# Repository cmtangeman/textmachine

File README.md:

# TextMachine
CrankPhone SW/FW/HW/Mech
Notes on directory structure:

FW:

ArduinoILI9341MKNNB1500 :  All for resistive touch FW (old)

capTouchTestingAndCal: testing calibration of capacitive touch

receiveSMSwithDebug:  debug file that doesn't need touchscreen

techmach: FW for old resistive screen

techmachcap: FW for current working capacitive touch screen.  See README.txt in this directory for further info.

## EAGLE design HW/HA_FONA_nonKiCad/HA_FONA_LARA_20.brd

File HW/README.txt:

Herein lies the HW, including board design, BOM, physical design, etc.  

The plan is to delta from the known working feather FONA board and fit it into current CrankLite PCB form factor.
This would make the physical design changes minimal, though a few cleanups to the physical design may occur.

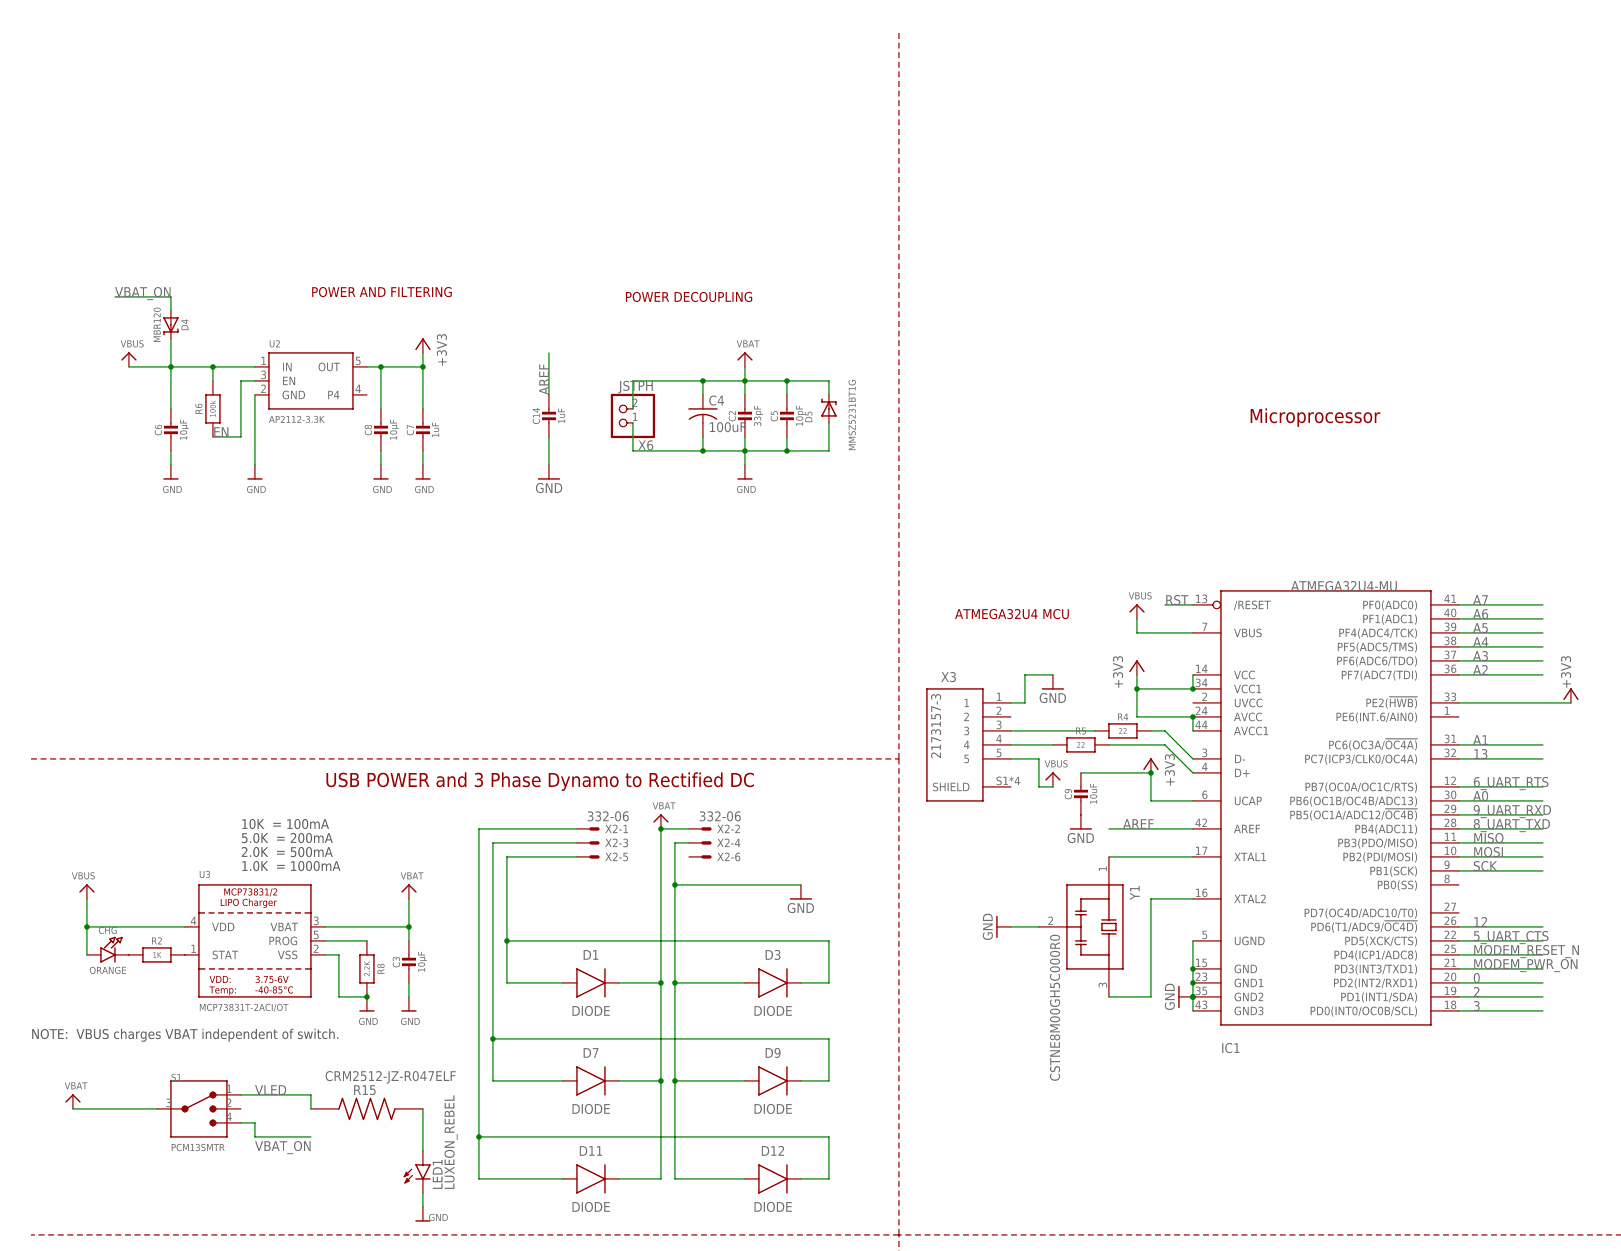
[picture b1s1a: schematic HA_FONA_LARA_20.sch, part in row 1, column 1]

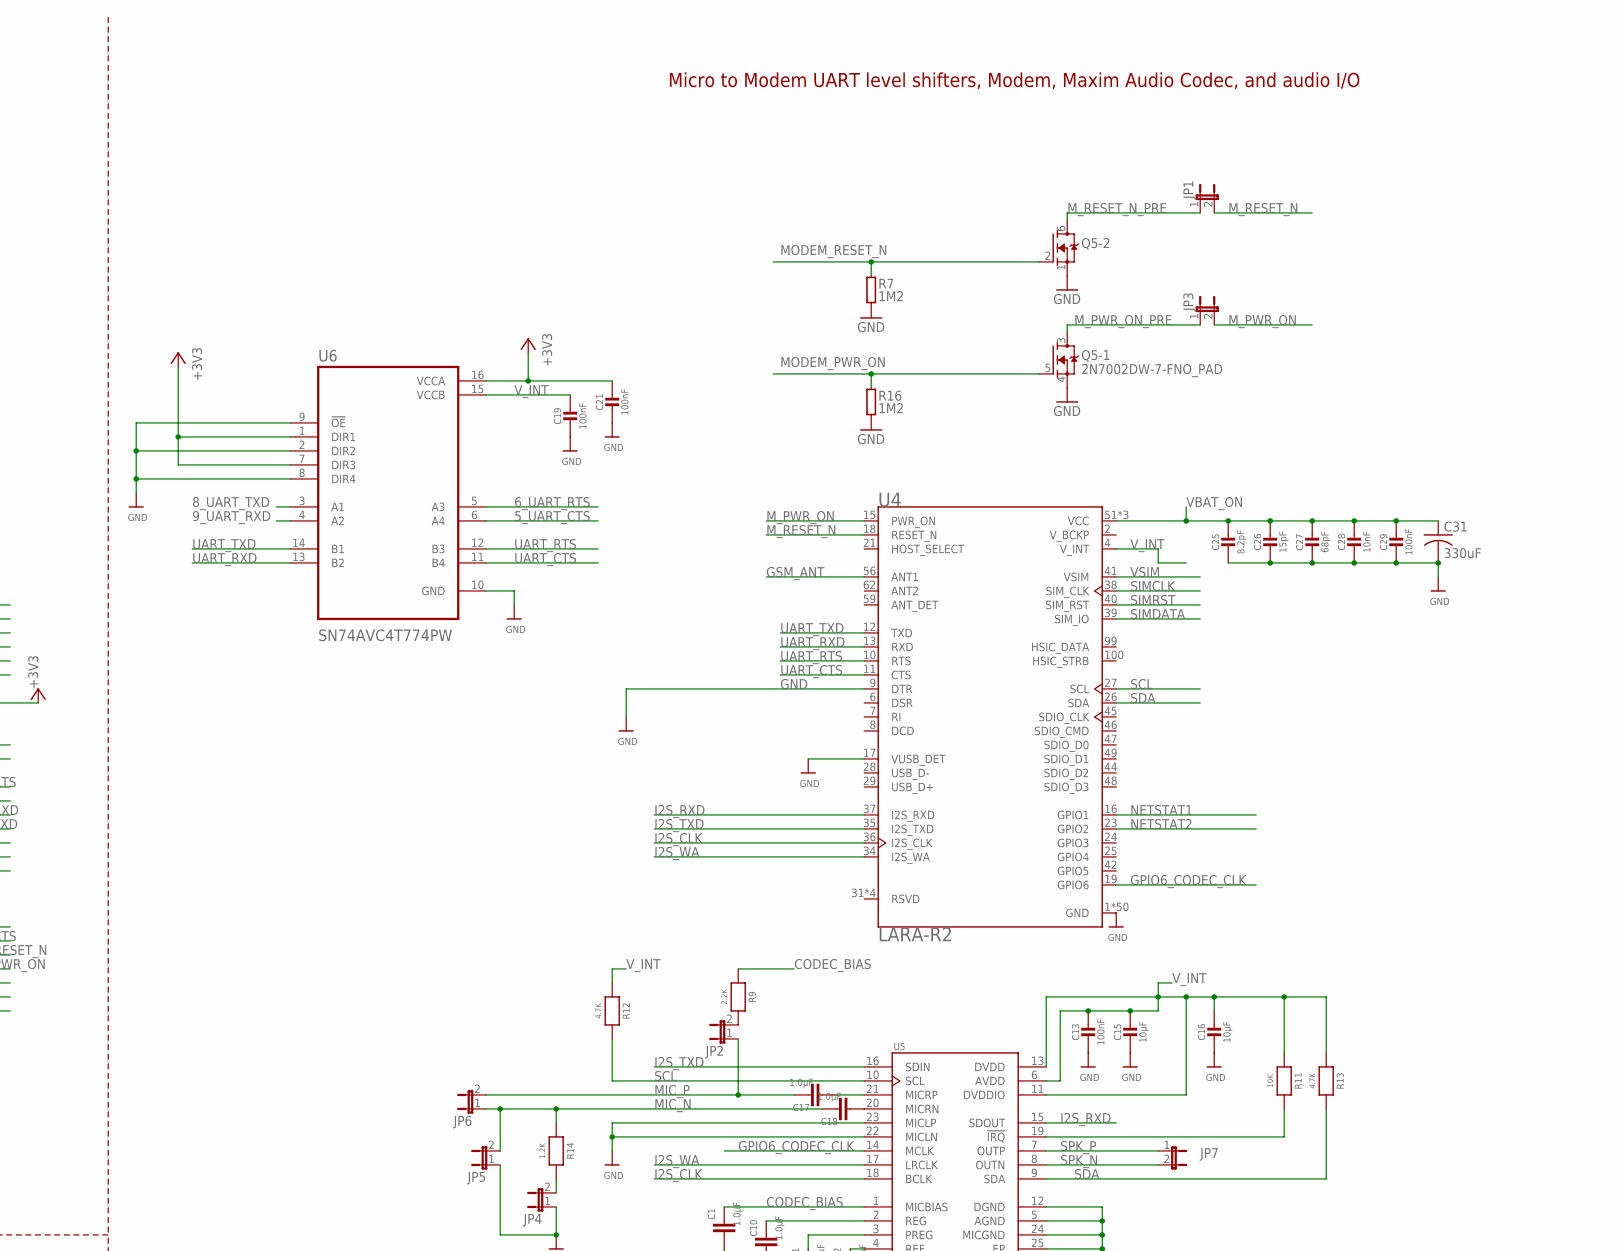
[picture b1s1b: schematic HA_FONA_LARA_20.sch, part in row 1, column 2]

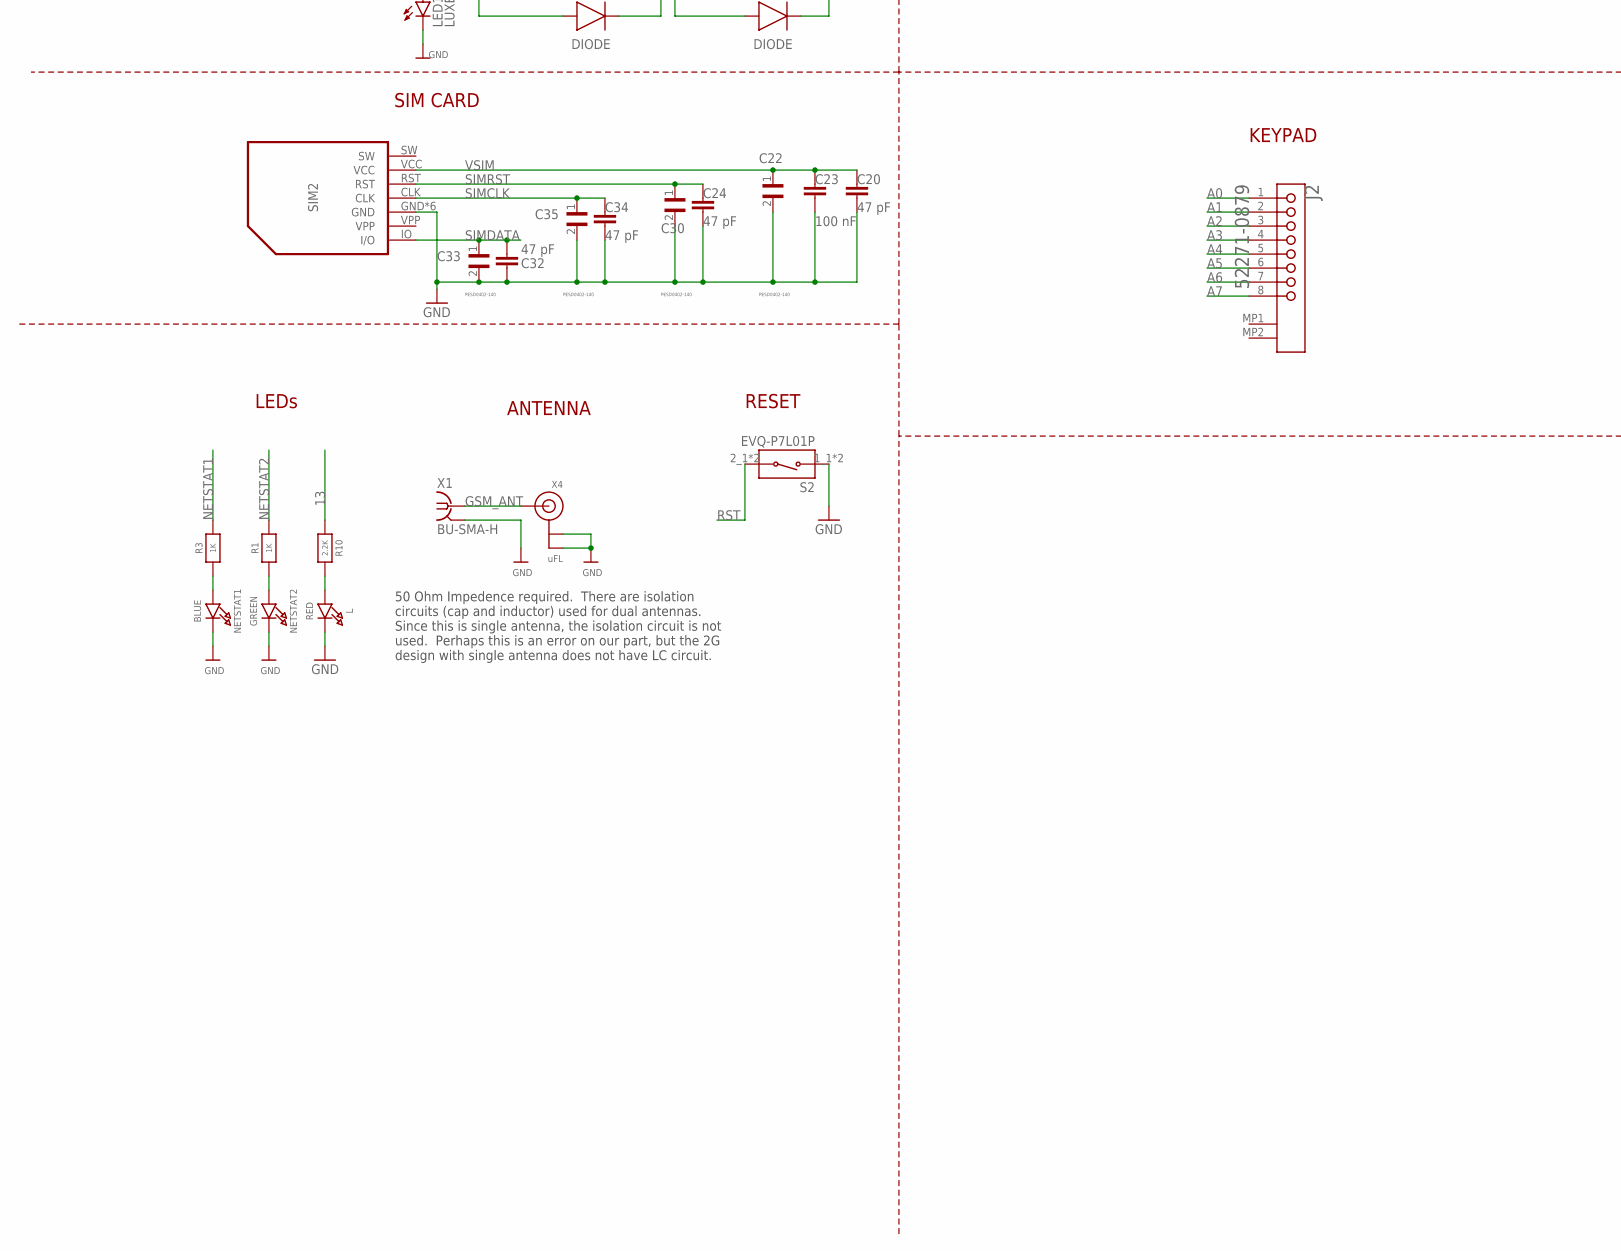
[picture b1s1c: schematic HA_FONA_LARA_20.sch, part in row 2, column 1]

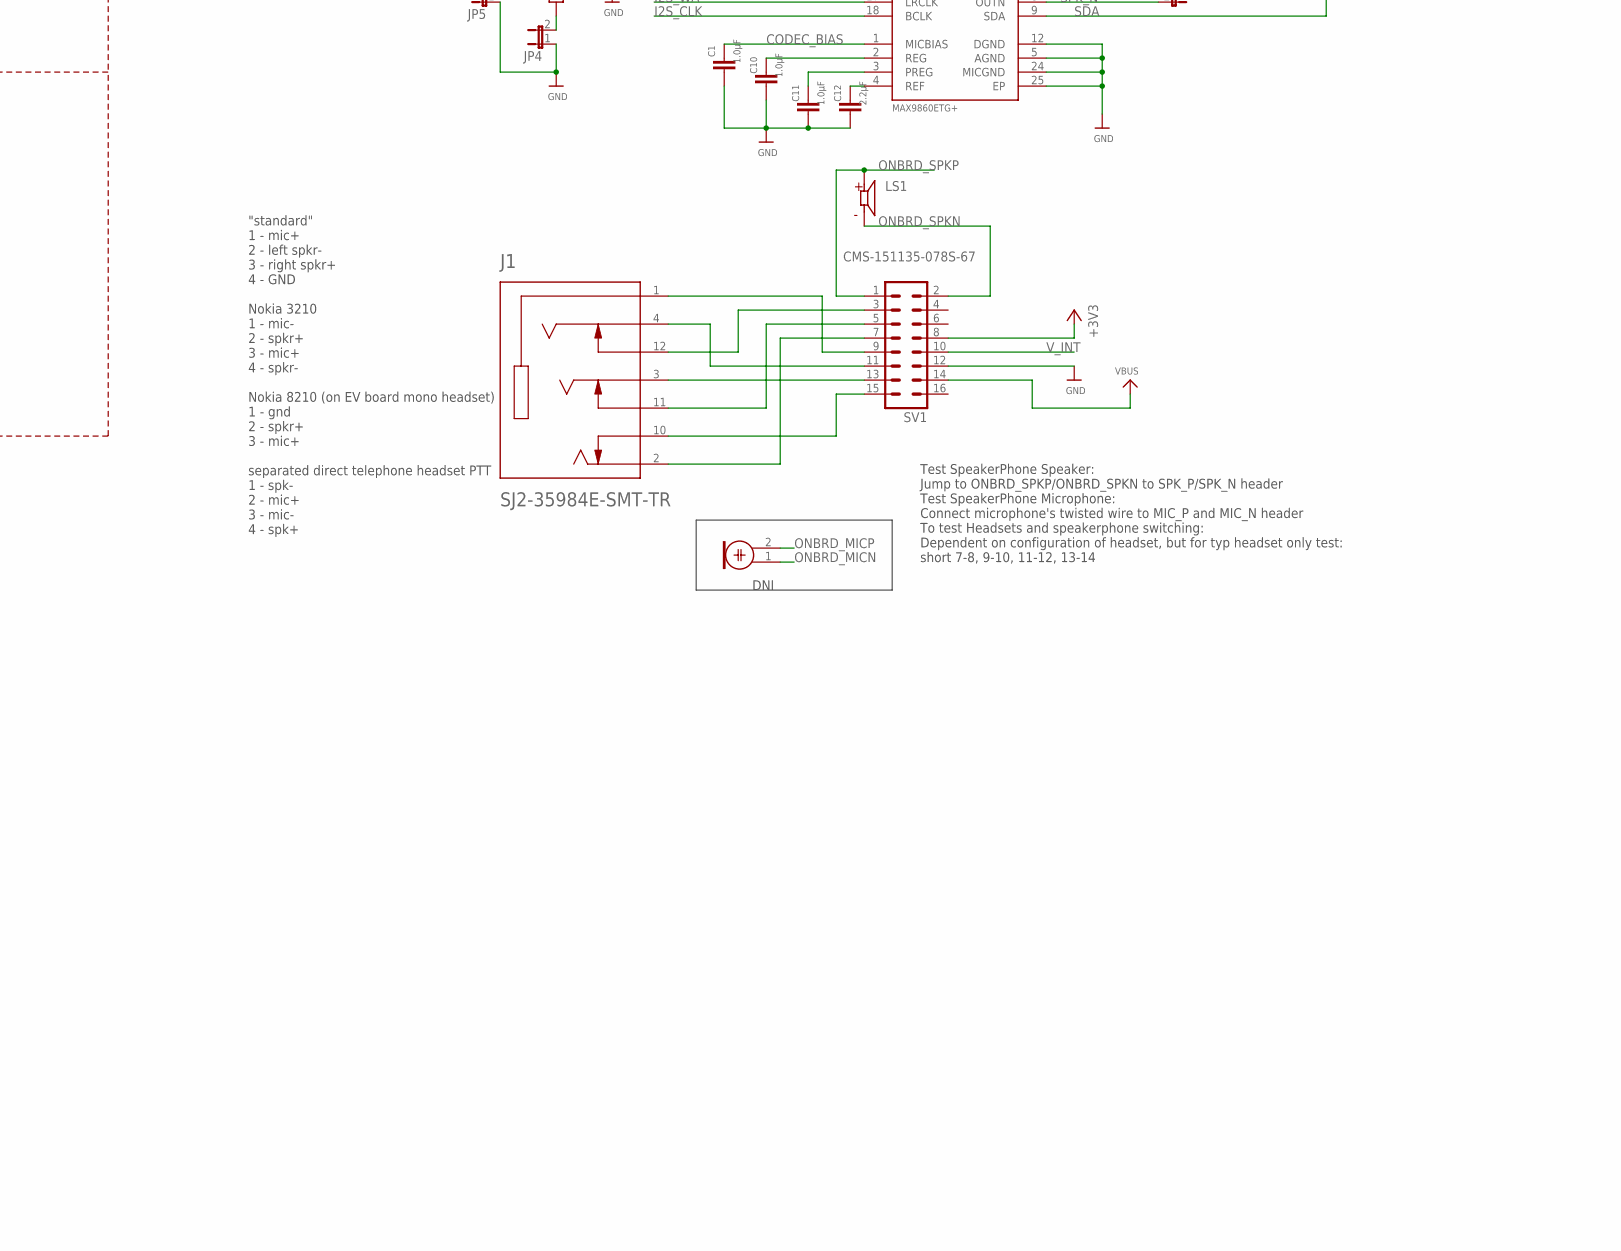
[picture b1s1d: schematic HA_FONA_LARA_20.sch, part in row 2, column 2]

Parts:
C1: 1.0µF; CAPC1005X60; MPN T491A225K016AT
C2: 33pF; 0805-NO; MPN 04025A330JAT2A
C3, C6, C8, C15, C16: 10µF; 0805-NO; MPN 08053D106KAT2A
C4: 100uF; C1210; MPN C1210C107M8PACTU
C5: 10pF; 0805-NO; MPN C0805C100D5GACTU
C7, C14: 1uF; 0603-NO; MPN 02016D104KAT2A
C9: 10uF; _0805MP; MPN 08053D106KAT2A
C10, C11, C17, C18: 1.0µF; CAPC1005X60; MPN 02016D104KAT2A
C12: 2.2µF; CAPC1608X85; MPN T491A225K016AT
C13: 100nF; 0805-NO; MPN 08055C104KAT2A
C19, C21, C29: 100nF; _0402; MPN C1005X7R1C104K050BC
C20, C24, C32, C34: 47 pF; CAPC1005X60
C22, C30, C33, C35: PESD0402-140; RESC1005X35N
C23: 100 nF; CAPC1005X60
C25: 8.2pF; _0402; MPN NMC0402NPO8R2C50TRPF
C26: 15pF; _0402; MPN MCMT15N150F500CT
C27: 68pF; _0402; MPN C0603C680J3GACAUTO
C28: 10nF; _0402; MPN 06035C103KAT2A
C31: 330uF; C1210; MPN GRM32EC80E337ME05L
CHG: ORANGE; CHIPLED_0805_NOOUTLINE; MPN KPT-2012SECK
D1, D3, D7, D9, D11, D12: DIODE; DIOM5336X265N
D4: MBR120; SOD-123; MPN MBR120VLSFT1G
D5: MMSZ5231BT1G; SOD-123; MPN MMSZ5231BT1G
IC1: ATMEGA32U4-MU; TQFN44_7MM; MPN ATMEGA32U4-MU
J1: SJ2-35984E-SMT-TR; CUI_SJ2-35984E-SMT-TR
J2: MOLEX_52271-0879MOLEX_52271-0879_0_0; MOLEX_52271-0879_0; MPN 52271-0879-CUT-TAPE
JP1, JP2, JP3, JP4, JP5, JP6, JP7: JP1E; JP1
L: RED; MICROBUILDER_CHIPLED_0603; MPN KPT-1608LVSECK-J3-PRV
LED1: LUXEON_REBEL
LS1: CMS-151135-078S-67; SPKR_CMS-151135-078S-67
M2: ELECTRET_MICROPHON-WM-61A; WM-61A
NETSTAT1: BLUE; CHIPLED_0805_NOOUTLINE; MPN KPT-2012LVVBC-D
NETSTAT2: GREEN; CHIPLED_0805_NOOUTLINE; MPN KPT-2012ZGCK
Q5: 2N7002DW-7-FNO_PAD; PWR_SC70-6L2
R1, R2, R3: 1K; 0603-NO; MPN ERJ3EKF1001V
R4, R5: 22; 0603-NO
R6: 100k; 0603-NO; MPN MCWR06X1003FTL
R7, R16: 1M2; 0402-1005X55N; MPN MCHVR02FTFY1204
R8, R9, R10: 2.2K; 0603-NO; MPN RC0603FR-072K2L.
R11: 10K; 0603-NO; MPN CRCW060310K0FKEA
R12, R13: 4.7K; 0603-NO; MPN ERJ-3EKF4701V
R14: 1.2K; 0603-NO; MPN CRCW06031K20FKEA
R15: CRM2512-JZ-R047ELF; RESC6331X80N
S1: PCM13SMTR; SW_PCM13SMTR; MPN PCM13SMTR
S2: EVQ-P7L01P; SW_EVQ-P7L01P; MPN EVQP7L01P
SIM2: -; MICROSIM8
SV1: MA08-2
U2: AP2112-3.3K; SOT23-5
U3: MCP73831T-2ACI/OT; SOT23-5; MPN MCP73831T-2ACI/OT
U4: LARA-R2; XCVR_LARA-R2
U5: MAX9860ETG+; QFN50P400X400X75-25N; MPN MAX9860ETG+
U6: SN74AVC4T774PW; SOP65P640X120-16N
X1: BU-SMA-H
X2: 332-06
X3: 2173157-3; CONN_2173157-3
X4: uFL; U.FL; MPN U.FL-R-SMT-1(10)
X6: JSTPH; JSTPH2
Y1: CSTNE8M00GH5C000R0; OSC_CSTNE8M00GH5C000R0

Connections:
0: IC1.20 (PD2(INT2/RXD1))
2: IC1.19 (PD1(INT1/SDA))
3: IC1.18 (PD0(INT0/OC0B/SCL))
5_UART_CTS: IC1.22 (PD5(XCK/CTS)), U6.6 (A4)
6_UART_RTS: IC1.12 (PB7(OC0A/OC1C/RTS)), U6.5 (A3)
8_UART_TXD: IC1.28 (PB4(ADC11)), U6.3 (A1)
9_UART_RXD: IC1.29 (PB5(OC1A/ADC12/!OC4B)), U6.4 (A2)
12: IC1.26 (PD6(T1/ADC9/!OC4D))
13: IC1.32 (PC7(ICP3/CLK0/OC4A)), R10.1
+3V3: C7.1, C8.1, C9.1, C21.1, IC1.6 (UCAP), IC1.14 (VCC), IC1.24 (AVCC), IC1.33 (PE2(!HWB)), IC1.34 (VCC1), IC1.44 (AVCC1), SV1.8, U2.5 (OUT), U6.1 (DIR1), U6.7 (DIR3), U6.16 (VCCA)
A0: IC1.30 (PB6(OC1B/OC4B/ADC13)), J2.1
A1: IC1.31 (PC6(OC3A/!OC4A)), J2.2
A2: IC1.36 (PF7(ADC7(TDI)), J2.3
A3: IC1.37 (PF6(ADC6/TDO)), J2.4
A4: IC1.38 (PF5(ADC5/TMS)), J2.5
A5: IC1.39 (PF4(ADC4/TCK)), J2.6
A6: IC1.40 (PF1(ADC1)), J2.7
A7: IC1.41 (PF0(ADC0)), J2.8
AREF: C14.1, IC1.42 (AREF)
CODEC_BIAS: C1.1, R9.1, U5.1 (MICBIAS)
D+: IC1.4 (D+), R5.2
D-: IC1.3 (D-), R4.2
EN: R6.1, U2.3 (EN)
GND: C1.2, C2.2, C3.2, C4.2, C5.2, C6.2, C7.2, C8.2, C9.2, C10.2, C11.2, C12.2, C13.2, C14.2, C15.2, C16.2, C19.2, C20.2, C21.2, C22.2, C23.2, C24.2, C25.2, C26.2, C27.2, C28.2, C29.2, C30.2, C31.2, C32.2, C33.2, C34.2, C35.2, D3.2 (A), D5.A, D9.2 (A), D12.2 (A), IC1.5 (UGND), IC1.15 (GND), IC1.23 (GND1), IC1.35 (GND2), IC1.43 (GND3), JP4.1, JP5.1, L.C, LED1.C, LED1.C@1 (C), NETSTAT1.C, NETSTAT2.C, Q5.1 (S), Q5.4 (S), R7.1, R8.2, R16.1, S2.1_1 (1), S2.1_2 (1), SIM2.GND, SIM2.SH1 (GND), SIM2.SH2 (GND), SIM2.SH3 (GND), SIM2.SH4 (GND), SIM2.SH5 (GND), SV1.12, U2.2 (GND), U3.2 (VSS), U4.1 (GND), U4.3 (GND), U4.5 (GND), U4.9 (DTR), U4.14 (GND), U4.17 (VUSB_DET), U4.20 (GND), U4.22 (GND), U4.30 (GND), U4.32 (GND), U4.43 (GND), U4.50 (GND), U4.54 (GND), U4.55 (GND), U4.57 (GND), U4.58 (GND), U4.60 (GND), U4.61 (GND), U4.63 (GND), U4.64 (GND), U4.65 (GND), U4.66 (GND), U4.67 (GND), U4.68 (GND), U4.69 (GND), U4.70 (GND), U4.71 (GND), U4.72 (GND), U4.73 (GND), U4.74 (GND), U4.75 (GND), U4.76 (GND), U4.77 (GND), U4.78 (GND), U4.79 (GND), U4.80 (GND), U4.81 (GND), U4.82 (GND), U4.83 (GND), U4.84 (GND), U4.85 (GND), U4.86 (GND), U4.87 (GND), U4.88 (GND), U4.89 (GND), U4.90 (GND), U4.91 (GND), U4.92 (GND), U4.93 (GND), U4.94 (GND), U4.95 (GND), U4.96 (GND), U5.5 (AGND), U5.12 (DGND), U5.22 (MICLN), U5.23 (MICLP), U5.24 (MICGND), U5.25 (EP), U6.2 (DIR2), U6.8 (DIR4), U6.9 (!OE), U6.10 (GND), X1.2, X1.3 (2), X1.4 (2), X1.5 (2), X2.4, X3.1, X4.1 (GND), X4.2 (GND), X6.1, Y1.2 (GND)
GPIO6_CODEC_CLK: U4.19 (GPIO6), U5.14 (MCLK)
GSM_ANT: U4.56 (ANT1), X1.1, X4.3 (SIGNAL)
I2S_CLK: U4.36 (I2S_CLK), U5.18 (BCLK)
I2S_RXD: U4.37 (I2S_RXD), U5.15 (SDOUT)
I2S_TXD: U4.35 (I2S_TXD), U5.16 (SDIN)
I2S_WA: U4.34 (I2S_WA), U5.17 (LRCLK)
MIC_N: C18.1, JP5.2, JP6.1, R14.1
MIC_P: C17.1, JP2.1, JP6.2
MISO: IC1.11 (PB3(PDO/MISO))
MODEM_PWR_ON: IC1.21 (PD3(INT3/TXD1)), Q5.5 (G), R16.2
MODEM_RESET_N: IC1.25 (PD4(ICP1/ADC8)), Q5.2 (G), R7.2
MOSI: IC1.10 (PB2(PDI/MOSI))
M_PWR_ON: JP3.2, U4.15 (PWR_ON)
M_PWR_ON_PRE: JP3.1, Q5.3 (D)
M_RESET_N: JP1.2, U4.18 (RESET_N)
M_RESET_N_PRE: JP1.1, Q5.6 (D)
unnamed: CHG.C, R2.1
unnamed: L.A, R10.2
unnamed: R2.2, U3.1 (STAT)
unnamed: R8.1, U3.5 (PROG)
unnamed: NETSTAT2.A, R1.1
unnamed: D11.2 (A), D12.1 (C), X2.1
unnamed: C17.2, U5.21 (MICRP)
unnamed: NETSTAT1.A, R3.1
unnamed: C12.1, U5.4 (REF)
unnamed: IC1.16 (XTAL2), Y1.3 (OUT)
unnamed: IC1.17 (XTAL1), Y1.1 (IN)
unnamed: C11.1, U5.3 (PREG)
unnamed: C10.1, U5.2 (REG)
unnamed: R5.1, X3.4
unnamed: R4.1, X3.3
unnamed: C18.2, U5.20 (MICRN)
unnamed: R11.2, U5.19 (!IRQ)
unnamed: JP2.2, R9.2
unnamed: JP4.2, R14.2
unnamed: D7.2 (A), D9.1 (C), X2.3
unnamed: D1.2 (A), D3.1 (C), X2.5
unnamed: J1.11 (RING1_SWITCH), SV1.5
unnamed: LED1.A, LED1.A@1 (A), R15.2
unnamed: J1.12 (RING2_SWITCH), SV1.3
unnamed: J1.2 (TIP), SV1.7
unnamed: J1.1 (SLEEVE), SV1.9
unnamed: J1.4 (RING2), SV1.11
unnamed: J1.3 (RING1), SV1.13
unnamed: J1.10 (TIP_SWITCH), SV1.15
NETSTAT1: R3.2, U4.16 (GPIO1)
NETSTAT2: R1.2, U4.23 (GPIO2)
ONBRD_MICN: M2.1
ONBRD_MICP: M2.2
ONBRD_SPKN: LS1.M, SV1.2
ONBRD_SPKP: LS1.P, SV1.1
RST: IC1.13 (/RESET), S2.2_1 (2), S2.2_2 (2)
SCK: IC1.9 (PB1(SCK))
SCL: R12.2, U4.27 (SCL), U5.10 (SCL)
SDA: R13.2, U4.26 (SDA), U5.9 (SDA)
SIMCLK: C34.1, C35.1, SIM2.CLK, U4.38 (SIM_CLK)
SIMDATA: C32.1, C33.1, SIM2.IO (I/O), U4.39 (SIM_IO)
SIMRST: C24.1, C30.1, SIM2.RST, U4.40 (SIM_RST)
SPK_N: JP7.2, U5.8 (OUTN)
SPK_P: JP7.1, U5.7 (OUTP)
UART_CTS: U4.11 (CTS), U6.11 (B4)
UART_RTS: U4.10 (RTS), U6.12 (B3)
UART_RXD: U4.13 (RXD), U6.13 (B2)
UART_TXD: U4.12 (TXD), U6.14 (B1)
VBAT: C2.1, C3.1, C4.1, C5.1, D1.1 (C), D5.C, D7.1 (C), D11.1 (C), S1.3, U3.3 (VBAT), X2.2, X6.2
VBAT_ON: C25.1, C26.1, C27.1, C28.1, C29.1, C31.1, D4.A, S1.4, U4.51 (VCC), U4.52 (VCC), U4.53 (VCC)
VBUS: C6.1, CHG.A, D4.C, IC1.7 (VBUS), R6.2, SV1.14, U2.1 (IN), U3.4 (VDD), X3.5
VLED: R15.1, S1.1
VSIM: C20.1, C22.1, C23.1, SIM2.VCC, U4.41 (VSIM)
V_BCKP: U4.2 (V_BCKP)
V_INT: C13.1, C15.1, C16.1, C19.1, R11.1, R12.1, R13.1, SV1.10, U4.4 (V_INT), U5.6 (AVDD), U5.11 (DVDDIO), U5.13 (DVDD), U6.15 (VCCB)

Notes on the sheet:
POWER AND FILTERING
RESET
ATMEGA32U4 MCU
10K = 100mA
5.0K = 200mA
2.0K = 500mA
1.0K = 1000mA
ANTENNA
SIM CARD
POWER DECOUPLING
LEDs
KEYPAD
USB POWER and 3 Phase Dynamo to Rectified DC
50 Ohm Impedence required. There are isolation circuits (cap and inductor) used for dual antennas. Since this is single antenna, the isolation circuit is not used. Perhaps this is an error on our part, but the 2G design with single antenna does not have LC circuit.
"standard" 1 - mic+ 2 - left spkr- 3 - right spkr+ 4 - GND Nokia 3210 1 - mic- 2 - spkr+ 3 - mic+ 4 - spkr- Nokia 8210 (on EV board mono headset) 1 - gnd 2 - spkr+ 3 - mic+ separated direct telephone headset PTT 1 - spk- 2 - mic+ 3 - mic- 4 - spk+
Test SpeakerPhone Speaker: Jump to ONBRD_SPKP/ONBRD_SPKN to SPK_P/SPK_N header Test SpeakerPhone Microphone: Connect microphone's twisted wire to MIC_P and MIC_N header To test Headsets and speakerphone switching: Dependent on configuration of headset, but for typ headset only test: short 7-8, 9-10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
NOTE: VBUS charges VBAT independent of switch.
Microprocessor
Micro to Modem UART level shifters, Modem, Maxim Audio Codec, and audio I/O
DNI

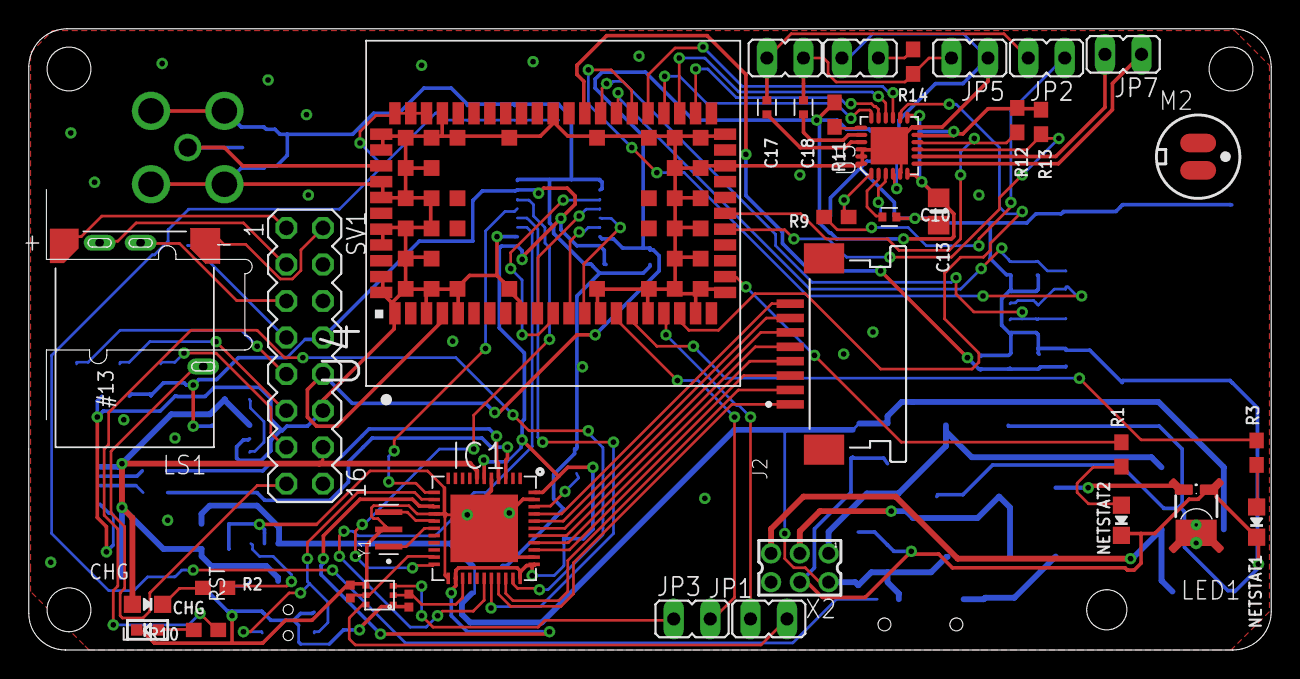
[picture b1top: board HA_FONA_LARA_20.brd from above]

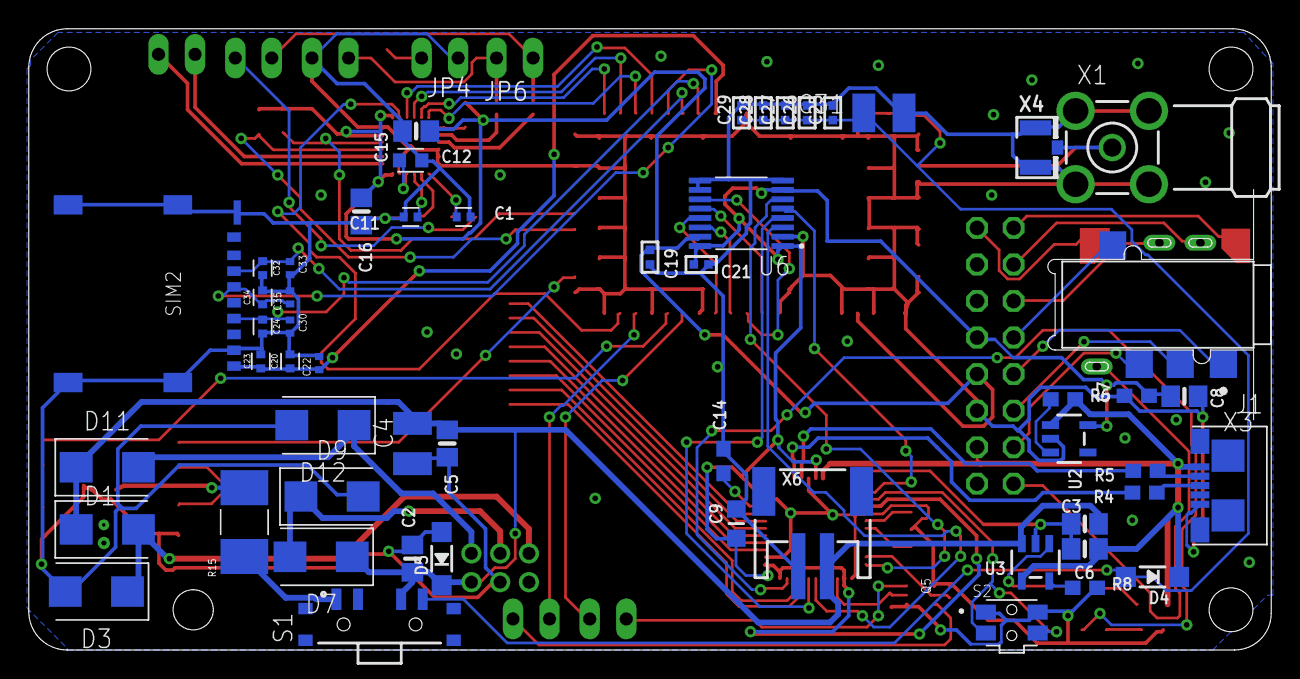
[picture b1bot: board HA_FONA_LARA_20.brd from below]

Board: 2 copper layers, 86.4 x 43.2 mm, 92 parts (55 on the bottom side), 85 nets.

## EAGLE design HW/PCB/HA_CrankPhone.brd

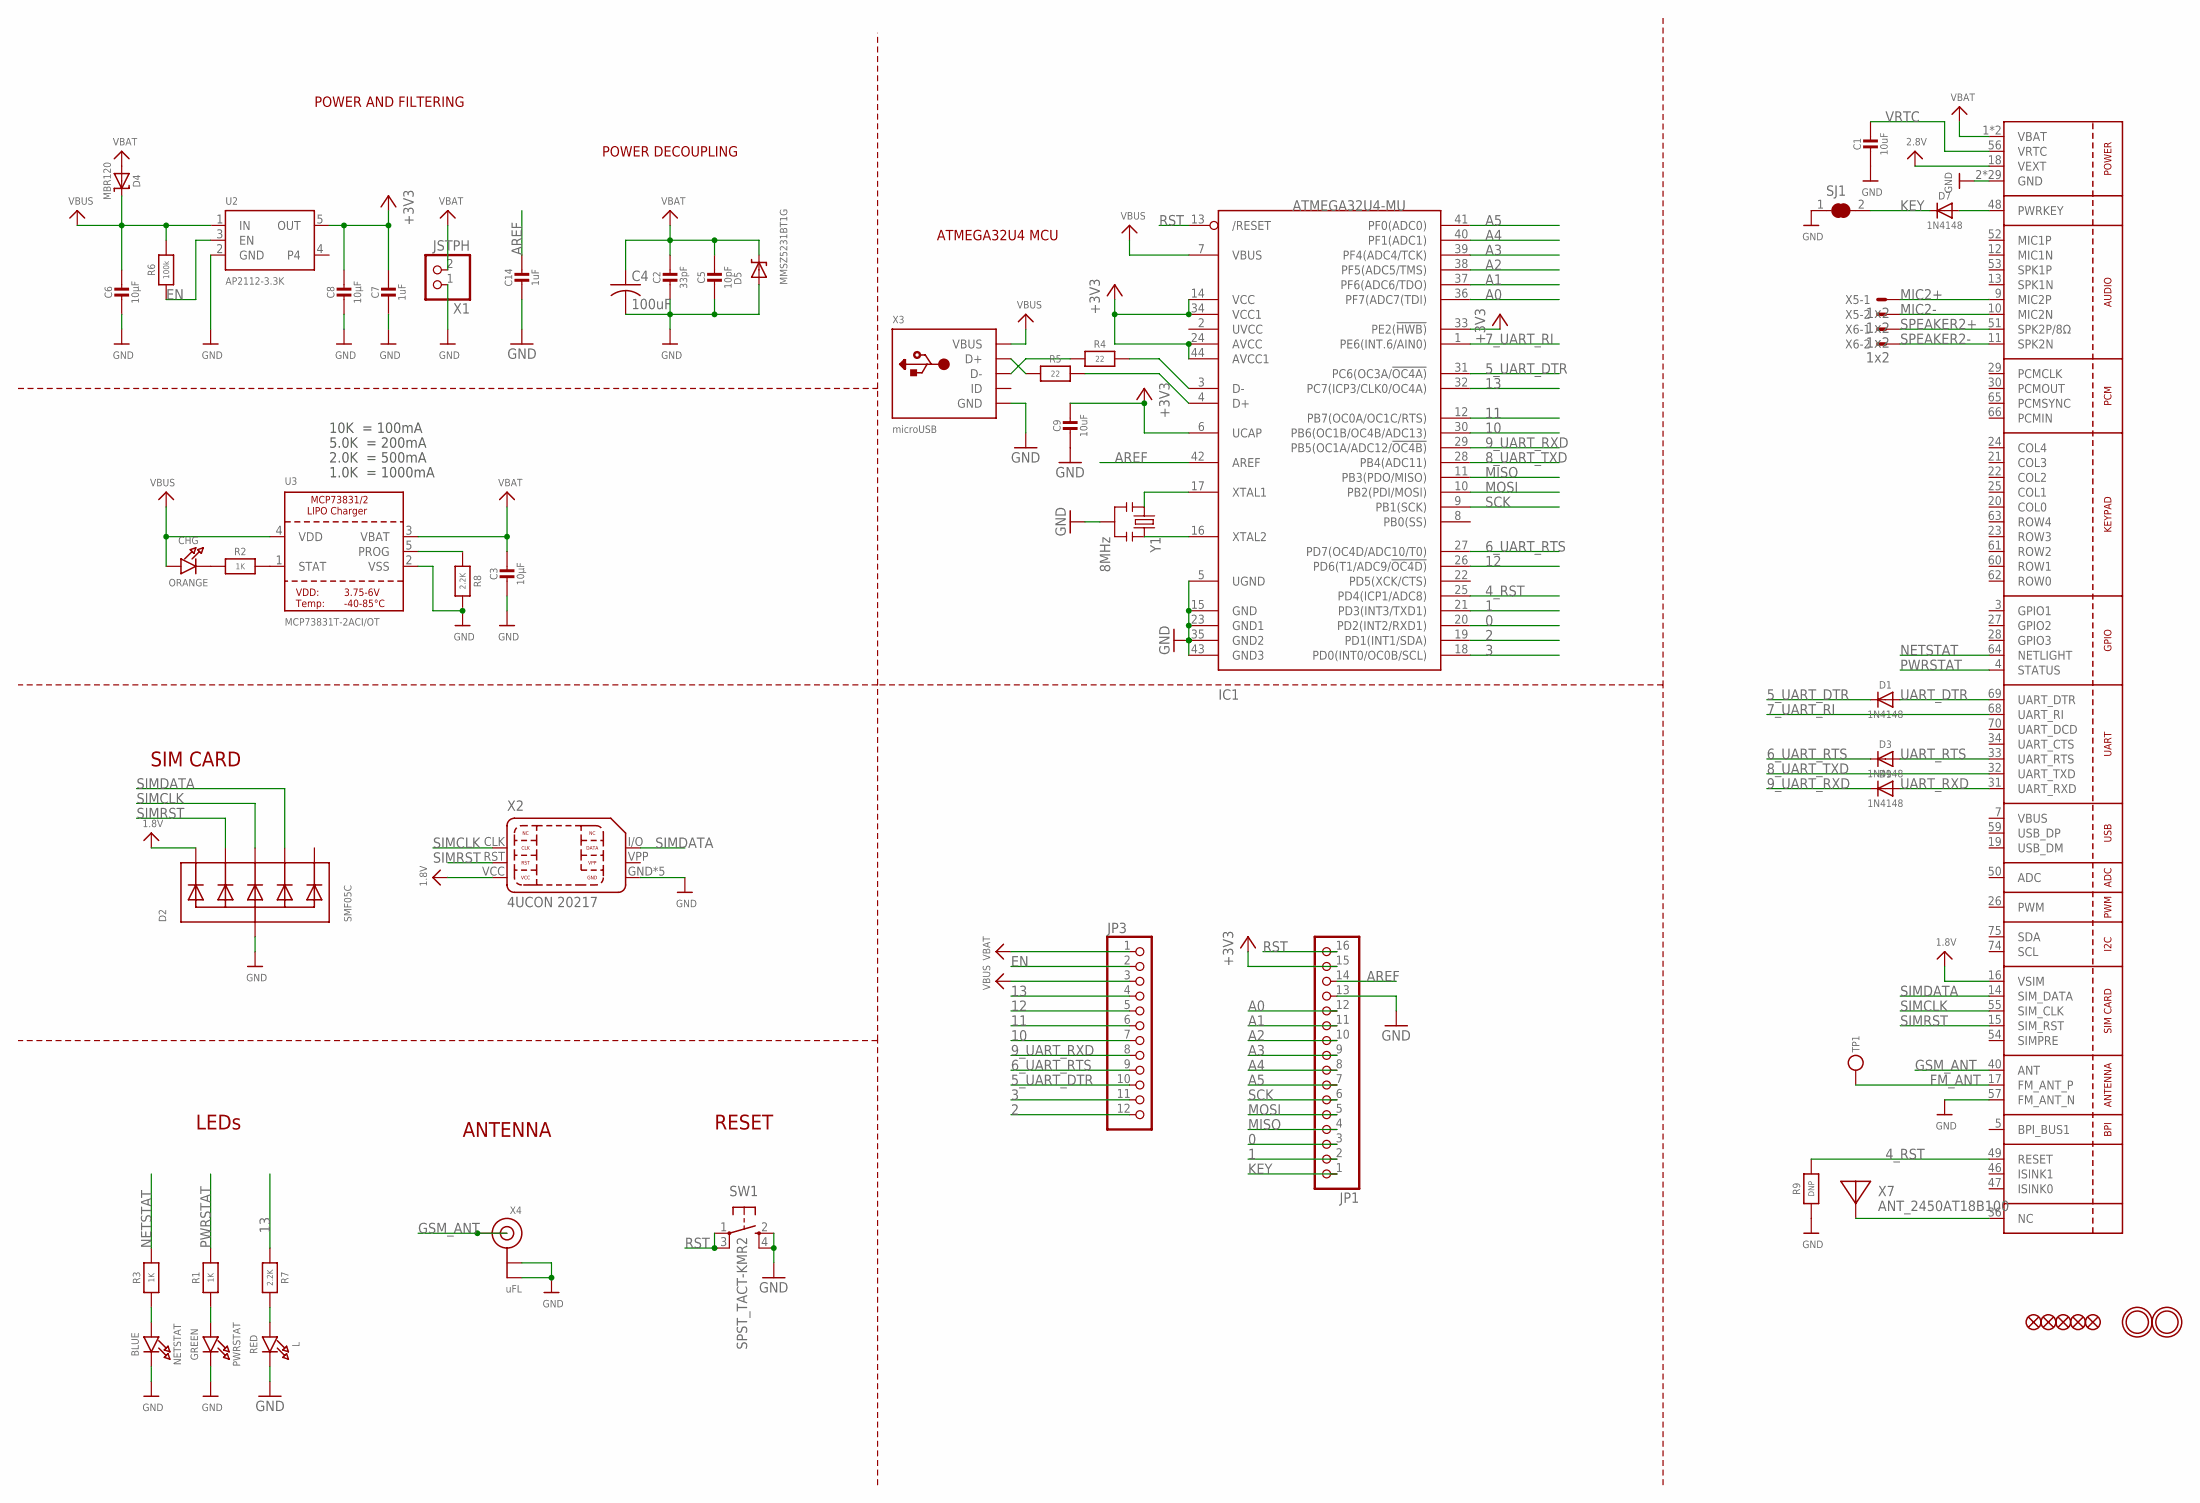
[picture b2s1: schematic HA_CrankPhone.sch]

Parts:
C1, C9: 10uF; _0805MP
C2: 33pF; 0805-NO
C3, C6, C8: 10µF; 0805-NO
C4: 100uF; C1210
C5: 10pF; 0805-NO
C7, C14: 1uF; 0603-NO
CHG: ORANGE; CHIPLED_0805_NOOUTLINE
D1, D3, D7, D9: 1N4148; SOD-323
D2: SMF05C; SOT363
D4: MBR120; SOD-123
D5: MMSZ5231BT1G; SOD-123
IC1: ATMEGA32U4-MU; TQFN44_7MM
JP1: HEADER-1X16ROUND; 1X16_ROUND
JP3: HEADER-1X12; 1X12_ROUND
L: RED; CHIPLED_0805_NOOUTLINE
NETSTAT: BLUE; CHIPLED_0805_NOOUTLINE
PWRSTAT: GREEN; CHIPLED_0805_NOOUTLINE
R1, R2, R3: 1K; 0603-NO
R4, R5: 22; 0603-NO
R6: 100k; 0603-NO
R7, R8: 2.2K; 0603-NO
R9: DNP; 0603-NO
SJ1: SOLDERJUMPER_CLOSED; SOLDERJUMPER_CLOSEDWIRE
SW1: SPST_TACT-KMR2; KMR2
TP1: TESTPOINTROUND1.5MM; TESTPOINT_ROUND_1.5MM
U1: SIM800H/L; SIM800L
U2: AP2112-3.3K; SOT23-5
U3: MCP73831T-2ACI/OT; SOT23-5
U$18, U$23, U$34, U$35, U$42: FIDUCIAL""; FIDUCIAL_1MM
U$31, U$32: MOUNTINGHOLE2.5; MOUNTINGHOLE_2.5_PLATED
X1: JSTPH; JSTPH2
X2: 4UCON 20217; 4UCONN_20217
X3: microUSB; 4UCONN_20329_V2
X4: uFL; U.FL
X5, X6: 1x2; 87758-0216
X7: ANT_2450AT18B100
Y1: 8MHz; RESONATOR-SMD

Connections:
0: IC1.20 (PD2(INT2/RXD1)), JP1.3
1: IC1.21 (PD3(INT3/TXD1)), JP1.2
1.8V: D2.1 (C1), U1.16 (VSIM), X2.VCC
2: IC1.19 (PD1(INT1/SDA)), JP3.12
2.8V: U1.18 (VEXT)
3: IC1.18 (PD0(INT0/OC0B/SCL)), JP3.11
4_RST: IC1.25 (PD4(ICP1/ADC8)), R9.2, U1.49 (RESET)
5_UART_DTR: D1.C, IC1.31 (PC6(OC3A/!OC4A)), JP3.10
6_UART_RTS: D3.C, IC1.27 (PD7(OC4D/ADC10/T0)), JP3.9
7_UART_RI: IC1.1 (PE6(INT.6/AIN0)), U1.68 (UART_RI)
8_UART_TXD: IC1.28 (PB4(ADC11)), U1.32 (UART_TXD)
9_UART_RXD: D9.C, IC1.29 (PB5(OC1A/ADC12/!OC4B)), JP3.8
10: IC1.30 (PB6(OC1B/OC4B/ADC13)), JP3.7
11: IC1.12 (PB7(OC0A/OC1C/RTS)), JP3.6
12: IC1.26 (PD6(T1/ADC9/!OC4D)), JP3.5
13: IC1.32 (PC7(ICP3/CLK0/OC4A)), JP3.4, R7.1
+3V3: C7.1, C8.1, C9.1, IC1.6 (UCAP), IC1.14 (VCC), IC1.24 (AVCC), IC1.33 (PE2(!HWB)), IC1.34 (VCC1), IC1.44 (AVCC1), JP1.15, U2.5 (OUT)
A0: IC1.36 (PF7(ADC7(TDI)), JP1.12
A1: IC1.37 (PF6(ADC6/TDO)), JP1.11
A2: IC1.38 (PF5(ADC5/TMS)), JP1.10
A3: IC1.39 (PF4(ADC4/TCK)), JP1.9
A4: IC1.40 (PF1(ADC1)), JP1.8
A5: IC1.41 (PF0(ADC0)), JP1.7
AREF: C14.1, IC1.42 (AREF), JP1.14
D+: IC1.4 (D+), R5.2
D-: IC1.3 (D-), R4.2
EN: JP3.2, R6.1, U2.3 (EN)
FM_ANT: TP1.P$1, U1.17 (FM_ANT_P)
GND: C1.2, C2.2, C3.2, C4.2, C5.2, C6.2, C7.2, C8.2, C9.2, C14.2, D2.2 (A), D5.A, IC1.5 (UGND), IC1.15 (GND), IC1.23 (GND1), IC1.35 (GND2), IC1.43 (GND3), JP1.13, L.C, NETSTAT.C, PWRSTAT.C, R8.2, R9.1, SJ1.1, SW1.2 (S), SW1.4 (S1), U1.2 (GND), U1.6 (GND), U1.8 (GND), U1.35 (GND), U1.37 (GND), U1.38 (GND), U1.39 (GND), U1.41 (GND), U1.43 (GND), U1.44 (GND), U1.45 (GND), U1.57 (FM_ANT_N), U1.58 (GND), U1.67 (GND), U1.71 (GND), U1.72 (GND), U1.73 (GND), U1.76 (GND), U1.77 (GND), U1.78 (GND), U1.79 (GND), U1.80 (GND), U1.81 (GND), U1.82 (GND), U1.83 (GND), U1.84 (GND), U1.85 (GND), U1.86 (GND), U1.87 (GND), U1.88 (GND), U2.2 (GND), U3.2 (VSS), X1.1, X2.GND, X2.GND@1 (GND), X2.GND@2 (GND), X2.GND@3 (GND), X2.GND@4 (GND), X3.BASE@1 (GND), X3.BASE@2 (GND), X3.GND, X3.SPRT@1 (GND), X3.SPRT@2 (GND), X3.SPRT@3 (GND), X3.SPRT@4 (GND), X4.1 (GND), X4.2 (GND), Y1.2
GSM_ANT: U1.40 (ANT), X4.3 (SIGNAL)
KEY: D7.C, JP1.1, SJ1.2
MIC2+: U1.9 (MIC2P), X5.1
MIC2-: U1.10 (MIC2N), X5.2
MISO: IC1.11 (PB3(PDO/MISO)), JP1.4
MOSI: IC1.10 (PB2(PDI/MOSI)), JP1.5
unnamed: CHG.C, R2.1
unnamed: L.A, R7.2
unnamed: R2.2, U3.1 (STAT)
unnamed: R8.1, U3.5 (PROG)
unnamed: PWRSTAT.A, R1.1
unnamed: U1.36 (NC), X7.FP
unnamed: D7.A, U1.48 (PWRKEY)
unnamed: NETSTAT.A, R3.1
unnamed: IC1.16 (XTAL2), Y1.3
unnamed: IC1.17 (XTAL1), Y1.1
unnamed: R5.1, X3.D+
unnamed: R4.1, X3.D-
NETSTAT: R3.2, U1.64 (NETLIGHT)
PWRSTAT: R1.2, U1.4 (STATUS)
RST: IC1.13 (/RESET), JP1.16, SW1.1, SW1.3 (P1)
SCK: IC1.9 (PB1(SCK)), JP1.6
SIMCLK: D2.4 (C3), U1.55 (SIM_CLK), X2.CLK
SIMDATA: D2.5 (C4), U1.14 (SIM_DATA), X2.I/O (DATA)
SIMRST: D2.3 (C2), U1.15 (SIM_RST), X2.RST
SPEAKER2+: U1.51 (SPK2P/8Ω), X6.1
SPEAKER2-: U1.11 (SPK2N), X6.2
UART_DTR: D1.A, U1.69 (UART_DTR)
UART_RTS: D3.A, U1.33 (UART_RTS)
UART_RXD: D9.A, U1.31 (UART_RXD)
VBAT: C2.1, C3.1, C4.1, C5.1, D4.A, D5.C, JP3.1, U1.1 (VBAT), U1.42 (VBAT), U3.3 (VBAT), X1.2
VBUS: C6.1, CHG.A, D4.C, IC1.7 (VBUS), JP3.3, R6.2, U1.7 (VBUS), U2.1 (IN), U3.4 (VDD), X3.VBUS
VRTC: C1.1, U1.56 (VRTC)

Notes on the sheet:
POWER AND FILTERING
RESET
ATMEGA32U4 MCU
10K = 100mA
5.0K = 200mA
2.0K = 500mA
1.0K = 1000mA
ANTENNA
SIM CARD
POWER DECOUPLING
LEDs

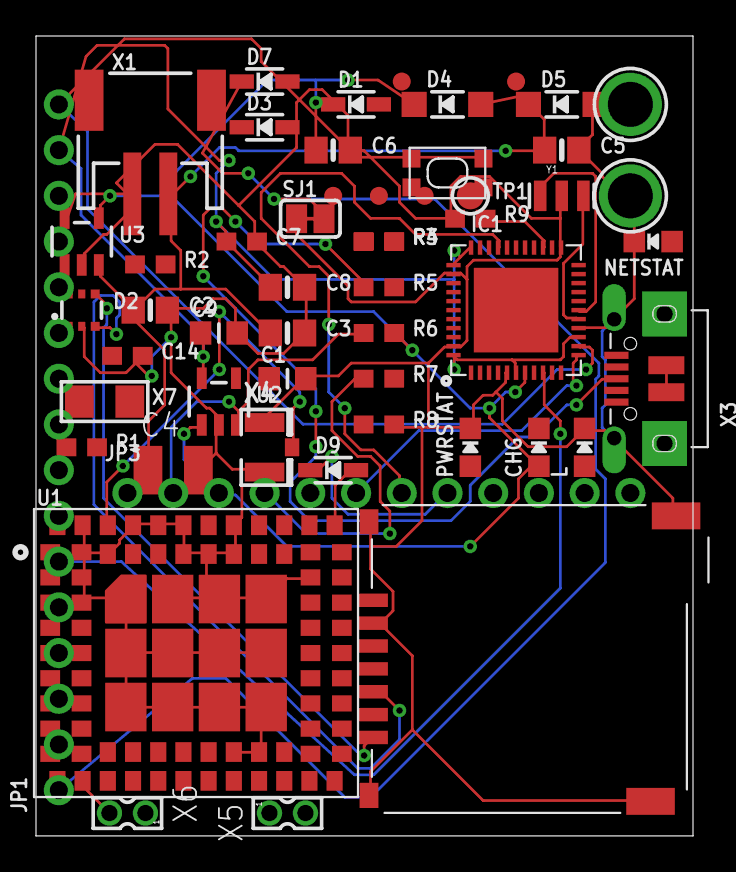
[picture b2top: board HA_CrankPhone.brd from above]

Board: 2 copper layers, 36.5 x 44.4 mm, 54 parts (0 on the bottom side), 61 nets.

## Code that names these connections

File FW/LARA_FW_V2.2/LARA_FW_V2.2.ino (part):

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 * 
 * https://www.arduino.cc/en/Hacking/PinMapping32u4
 * 
  _BV(2), // D0 - PD2
  _BV(3), // D1 - PD3
  _BV(1), // D2 - PD1
  _BV(0), // D3 - PD0
  _BV(4), // D4 - PD4
  _BV(6), // D5 - PC6
  _BV(7), // D6 - PD7
  _BV(6), // D7 - PE6

  _BV(4), // D8 - PB4
  _BV(5), // D9 - PB5
  _BV(6), // D10 - PB6
  _BV(7), // D11 - PB7
  _BV(6), // D12 - PD6
  _BV(7), // D13 - PC7

  _BV(3), // D14 - MISO - PB3
  _BV(1), // D15 - SCK - PB1
  _BV(2), // D16 - MOSI - PB2
  _BV(0), // D17 - SS - PB0

  _BV(7), // D18 - A0 - PF7
  _BV(6), // D19 - A1 - PF6
  _BV(5), // D20 - A2 - PF5
  _BV(4), // D21 - A3 - PF4
  _BV(1), // D22 - A4 - PF1
  _BV(0), // D23 - A5 - PF0

  _BV(4), // D24 / D4 - A6 - PD4
  _BV(7), // D25 / D6 - A7 - PD7
  _BV(4), // D26 / D8 - A8 - PB4
  _BV(5), // D27 / D9 - A9 - PB5
  _BV(6), // D28 / D10 - A10 - PB6
  _BV(6), // D29 / D12 - A11 - PD6
  */
void setup() {
//vcc
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  Serial.println(F("HA Phone1 is OK"));
        delay(1000);              // wait 
        digitalWrite(13, LOW);    // turn the LED off by making the voltage LOW
        if (!ha_fona.setGPIO(16,2,0)) { // turn on GPIO1 for netstat
          //Serial.println(F("GPIO 1 Set Failed"));
          Serial.println(F(" "));
        } else {
          Serial.println(F("GPIO 1 Set!"));
        }        
        if (!ha_fona.setGPIO(23,0,1)) {  // turn on GPIO2 for battery charge 
          //Serial.println(F("GPIO 1 Set Failed"));
          Serial.println(F(" "));
        } else {
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
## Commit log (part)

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2026-01-21 Inital commit
2026-01-31 Removed crankphone stuff, creating a cleaner repository with just text machine stuff
2026-02-06 Adding csv with components descriptioins
2026-02-06 Organizing
2026-02-07 Serial logic done, transferring to tft
2026-02-11 Working touchscreen / display functionalllity
2026-02-14 Keyboard progress
2026-02-15 More keyboard progess, first text through GUI sent
2026-02-16 Keyboard sending texts, working through receive function, beggining implemtntationa of recent messages, contacs, once thats solidified move on to SD memory saving
2026-02-17 Implementation of recent messages UI
2026-02-25 Improvements to touchscreen detection keyboard (1hr)
2026-02-26 Fixed 0,0 garbage reading by adding new debouncing logic
2026-02-26 Added new UI_COMPOSE logic such that SEND is no longer the transition variable between msg input and phone number input, instead use standard method of clicking between the two input boxes to switch 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
2026-03-14 Added fonts, new keyboard, karat
2026-03-15 Reworking Messages and conversation modules, fixed touch bleedthrough for conversation and messages
2026-04-02 Added documentation - Design idea is to go off of crankLight altering the dimensions to match the TFT LCD touchscreen
2026-05-03 Create README.txt
    bit of description of files.
2026-05-03 Added PSM logic and install dependencies text file
2026-05-18 Added timestamp logic for messages and cleand up message thread logic. TODO for tommmorow: implement contact logic using serial monitor and SD card non volatile memory storage with csv file [4 hours]
2026-05-19 Added homescreen clock and CSQ RSSI meter for home screen as well, timestamp logic still needs to be cleaned up
2026-06-23 Added # checking to ensure e.164 format so no duplicate conversation
2026-06-26 Added contact name check in compose step
2026-06-29 Added scrolling functionality for contacts screen

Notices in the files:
FW/LARA_FW_V2.2/LARA_FW_V2.2.ino:
BSD license, all text above must be included in any redistribution
parts and their libraries:
microbuilder: This work is placed in the public domain, and may be freely used for commercial and non-commercial work with the following conditions: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
Arduino-transistors: Copyright (c) 2016-2017 Arduino LLC.  All right reserved.
